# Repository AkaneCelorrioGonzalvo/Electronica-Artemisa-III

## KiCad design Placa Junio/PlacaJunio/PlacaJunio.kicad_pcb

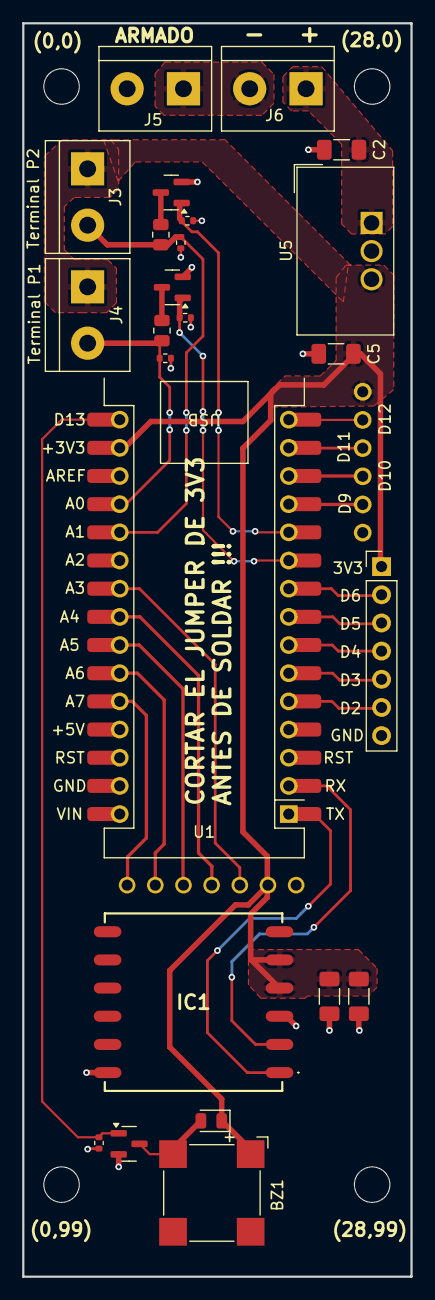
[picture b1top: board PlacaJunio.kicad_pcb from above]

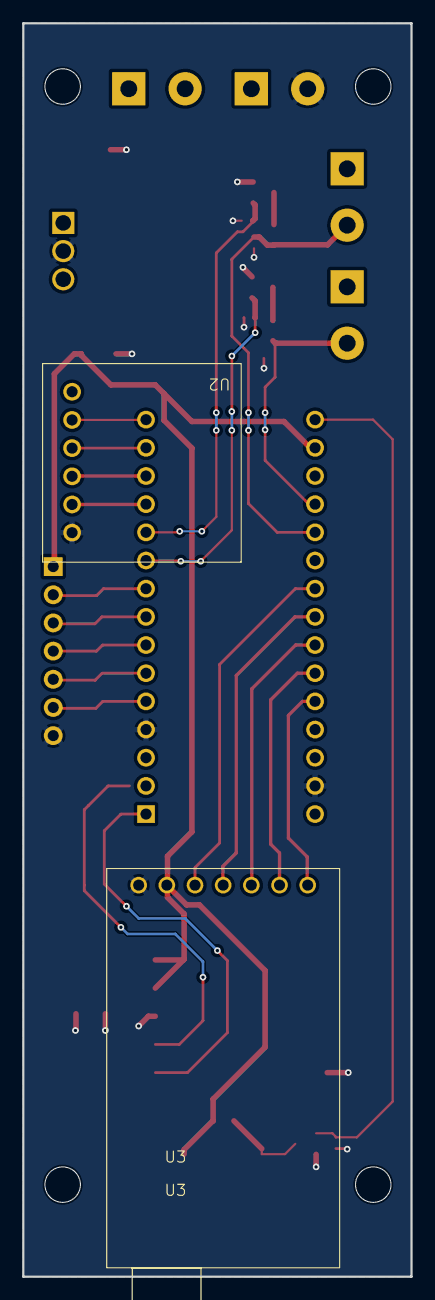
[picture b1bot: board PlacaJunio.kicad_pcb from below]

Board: 2 copper layers, 35.0 x 113.0 mm, 30 parts (2 on the bottom side), 28 nets.

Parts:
BZ1: Buzzer; MagneticBuzzer_CUI_CMT-8504-100-SMT
C2, C5, C6: 10uF; C_1206_3216Metric_Pad1.33x1.80mm_HandSolder
C7: 100nF; C_1206_3216Metric_Pad1.33x1.80mm_HandSolder
D1: D; D_0805_2012Metric
H1, H2, H3, H4: MountingHole; MountingHole_3.2mm_M3_DIN965
IC1: LC86LICMD
J1: Conn_01x07_Pin; PinHeader_1x07_P2.54mm_Vertical
J3: Terminal P2; TerminalBlock_bornier-2_P5.08mm
J4: Terminal P1; TerminalBlock_bornier-2_P5.08mm
J5: Terminal P3; TerminalBlock_bornier-2_P5.08mm
J6: Terminal P4; TerminalBlock_bornier-2_P5.08mm
Q2, Q3, Q4: IRLML0030; SOT-23
R5, R7, R9: 10k; R_0402_1005Metric
R14, R17: 3.3 Ohm 1%; R_0805_2012Metric
R15, R18: 1M; R_0402_1005Metric
U1: Nano BLE 33 Sense
U2: MicroSD
U3: LoRa
U5: TSR2-2433N; Converter_DCDC_TRACO_TSR2-24xxN_TSR2-24xxxN_THT

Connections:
+3V3: BZ1.1 (+), C5.1, C6.1, C7.1, D1.1 (K), IC1.4 (VCC), IC1.5 (V_BCKP), J1.1, J3.1, J4.1, U1.2 (+3v3), U2.6 (VCC), U3.6 (VCC), U5.3 (Vout)
+BATT: C2.1, J6.1, U5.1 (Vin)
/Aux: U1.7 (A3), U3.5 (AUX)
/Buzzer: Q4.1 (G), R9.1, U1.1 (D_13)
/D2: J1.6, U1.20 (D2)
/D3: J1.5, U1.21 (D3)
/D4: J1.4, U1.22 (D4)
/D5: J1.3, U1.23 (D5)
/D6: J1.2, U1.24 (D6)
/M0_LoRa: U1.11 (A7), U3.1 (M0)
/M1_LoRa: U1.10 (A6), U3.2 (M1)
/MISO: U1.27 (D9), U2.2 (MISO)
/MOSI: U1.29 (D11), U2.4 (MOSI)
/PARACAIDAS 1: Q3.1 (G), R7.1, U1.25 (D7)
/PARACAIDAS 2: Q2.1 (G), R5.1, U1.26 (D8)
/RX_GPS: IC1.1 (RXD), U1.16 (TX)
/RX_LoRa: U1.9 (A5), U3.3 (RX)
/SCK: U1.28 (D10), U2.3 (SCK)
/SD_CS: U1.30 (D12), U2.5 (CS)
/SENSE 1: J4.2, R14.1, R15.1, U1.4 (A0)
/SENSE 2: J3.2, R17.1, R18.1, U1.5 (A1)
/TX_GPS: IC1.2 (TXD), U1.17 (RX)
/TX_LoRa: U1.8 (A4), U3.4 (TX)
GND: C2.2, C5.2, C6.2, C7.2, IC1.3 (GND_1), IC1.12 (GND_2), J1.7, J5.2, Q2.2 (S), Q3.2 (S), Q4.2 (S), R5.2, R7.2, R9.2, R15.2, R18.2, U1.14 (GND), U1.19 (GND), U2.1 (GND), U3.7 (GND), U5.2 (GND)
unnamed: BZ1.2 (-), D1.2 (A), Q4.3 (D)
unnamed: J5.1, J6.2
unnamed: Q2.3 (D), R17.2
unnamed: Q3.3 (D), R14.2

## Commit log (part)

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2026-06-18 Placa
2026-06-18 Cambios PCB
2026-06-18 Cambios
2026-06-23 Update Placa
2026-06-23 Schematic distinto
2026-06-23 Test
2026-06-23 Esquemático Completo
2026-06-23 Actualización LoRa
2026-06-23 Primera version
2026-06-23 Elementos posicionados
2026-06-23 Cambio de posición de componenentes
2026-06-27 Ruteando
2026-06-27 Version 1
2026-06-27 Primera versión definitiva
2026-06-29 V1 definitiva
2026-06-29 V1 definitiiva ya seguro
2026-06-30 Cambios recientes
2026-06-30 Actualización Placa
2026-06-30 Actualización Con Placa Dani 1/2
2026-06-30 Cambios Placa Daniel 2/2
